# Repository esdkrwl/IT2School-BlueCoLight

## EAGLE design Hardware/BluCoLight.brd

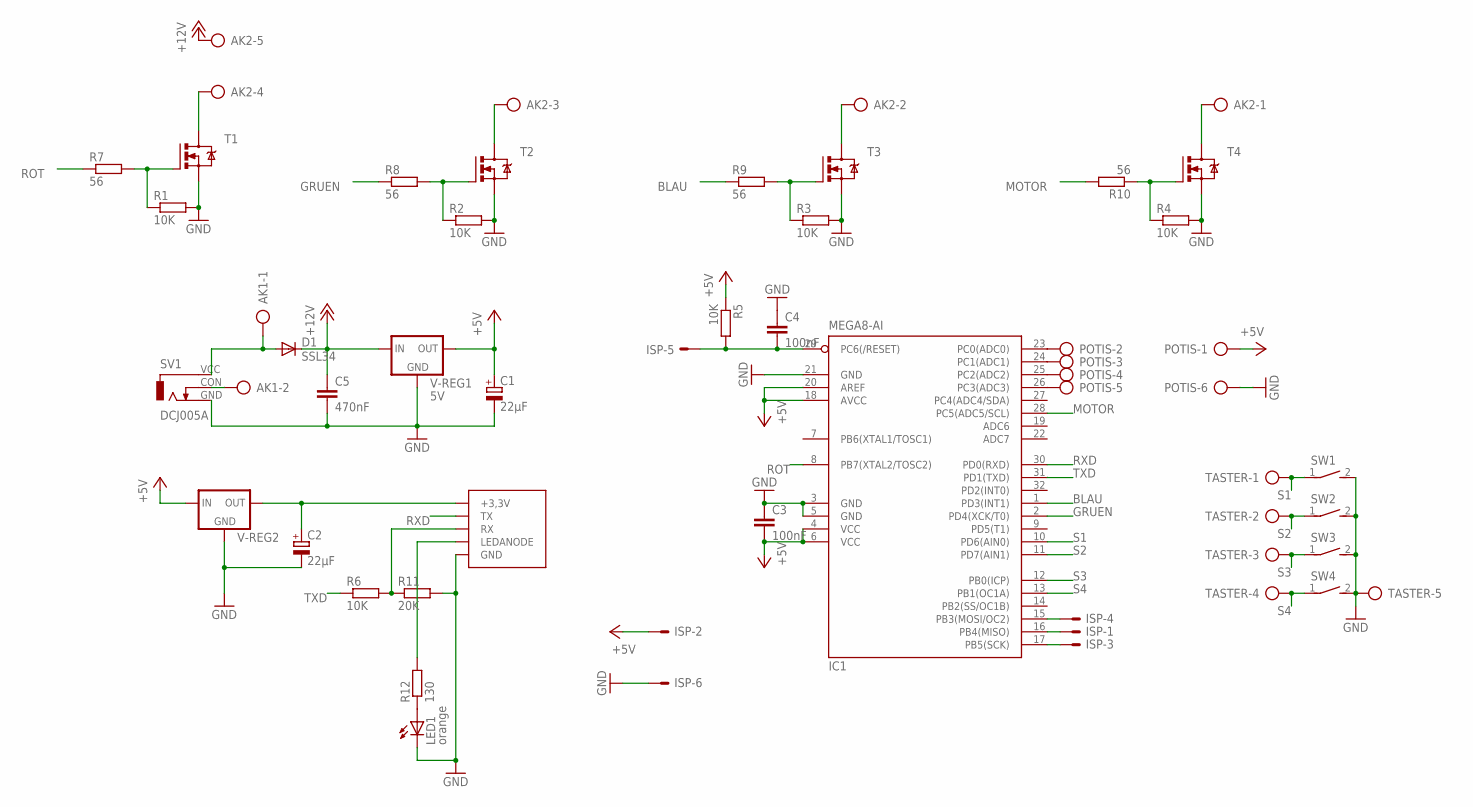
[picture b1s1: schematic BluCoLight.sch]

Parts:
AK1: AK2; AK/2
AK2: AK5AK/5; AK/5
C1, C2: 22µF; 153CLV-0605
C3, C4: 100nF; C0805K
C5: 470nF; C1210K
D1: SSL34; SMC
HC-06: HC-06; HC-06SMD
IC1: MEGA8-AI; TQFP32-08
ISP: ML6E; ML6
LED1: orange; CHIP-LED0603
POTIS: AK6PAD/6; PAD/6
R1, R2, R3, R4, R5, R6: 10K; R0603
R7, R8, R9, R10: 56; R0603
R11: 20K; R0603
R12: 130; R0603
SV1: DCJ005A; DC005A
SW1, SW2, SW3, SW4: TASTER36SMD; 3*6*2.5SMD_TASTER
T1, T2, T3, T4: IRLZ34NSPBFD2PACK; D2PACK
TASTER: AK5PAD/5; PAD/5
V-REG1: 5V; SOT223
V-REG2: AMS1117-3.3SOT223; SOT223

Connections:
+5V: C1.+, C3.2, IC1.4 (VCC), IC1.6 (VCC), IC1.18 (AVCC), IC1.20 (AREF), ISP.2, POTIS.1, R5.1, V-REG1.3 (OUT), V-REG2.3 (IN)
+12V: AK2.5, C5.1, D1.C, V-REG1.1 (IN)
BLAU: IC1.1 (PD3(INT1)), R9.1
GND: C1.-, C2.-, C3.1, C4.1, C5.2, HC-06.P$13 (GND), HC-06.P$21 (GND), HC-06.P$22 (GND), IC1.3 (GND), IC1.5 (GND), IC1.21 (GND), ISP.6, LED1.C, POTIS.6, R1.2, R2.2, R3.2, R4.2, R11.2, SV1.GND (3), SW1.2 (S), SW2.2 (S), SW3.2 (S), SW4.2 (S), T1.3 (S), T2.3 (S), T3.3 (S), T4.3 (S), TASTER.5, V-REG1.2 (GND), V-REG1.4 (GND), V-REG2.1 (GND)
GRUEN: IC1.2 (PD4(XCK/T0)), R8.1
MOTOR: IC1.28 (PC5(ADC5/SCL)), R10.2
unnamed: HC-06.P$24 (LEDANODE), R12.2
unnamed: C4.2, IC1.29 (PC6(/RESET)), ISP.5, R5.2
unnamed: R2.1, R8.2, T2.1 (G)
unnamed: IC1.15 (PB3(MOSI/OC2)), ISP.4
unnamed: R1.1, R7.2, T1.1 (G)
unnamed: AK2.4, T1.2 (D)
unnamed: AK2.3, T2.2 (D)
unnamed: R4.1, R10.1, T4.1 (G)
unnamed: IC1.16 (PB4(MISO)), ISP.1
unnamed: R3.1, R9.2, T3.1 (G)
unnamed: AK2.2, T3.2 (D)
unnamed: IC1.17 (PB5(SCK)), ISP.3
unnamed: AK2.1, T4.2 (D)
unnamed: HC-06.P$2 (RX), R6.2, R11.1
unnamed: LED1.A, R12.1
unnamed: IC1.23 (PC0(ADC0)), POTIS.2
unnamed: IC1.24 (PC1(ADC1)), POTIS.3
unnamed: C2.+, HC-06.P$12 (+3,3V), V-REG2.2 (OUT), V-REG2.4 (OUT)
unnamed: IC1.25 (PC2(ADC2)), POTIS.4
unnamed: IC1.26 (PC3(ADC3)), POTIS.5
unnamed: AK1.2, SV1.CON (2)
unnamed: AK1.1, D1.A, SV1.VCC (1)
ROT: IC1.8 (PB7(XTAL2/TOSC2)), R7.1
RXD: HC-06.P$1 (TX), IC1.30 (PD0(RXD))
S1: IC1.10 (PD6(AIN0)), SW1.1, TASTER.1
S2: IC1.11 (PD7(AIN1)), SW2.1, TASTER.2
S3: IC1.12 (PB0(ICP)), SW3.1, TASTER.3
S4: IC1.13 (PB1(OC1A)), SW4.1, TASTER.4
TXD: IC1.31 (PD1(TXD)), R6.1

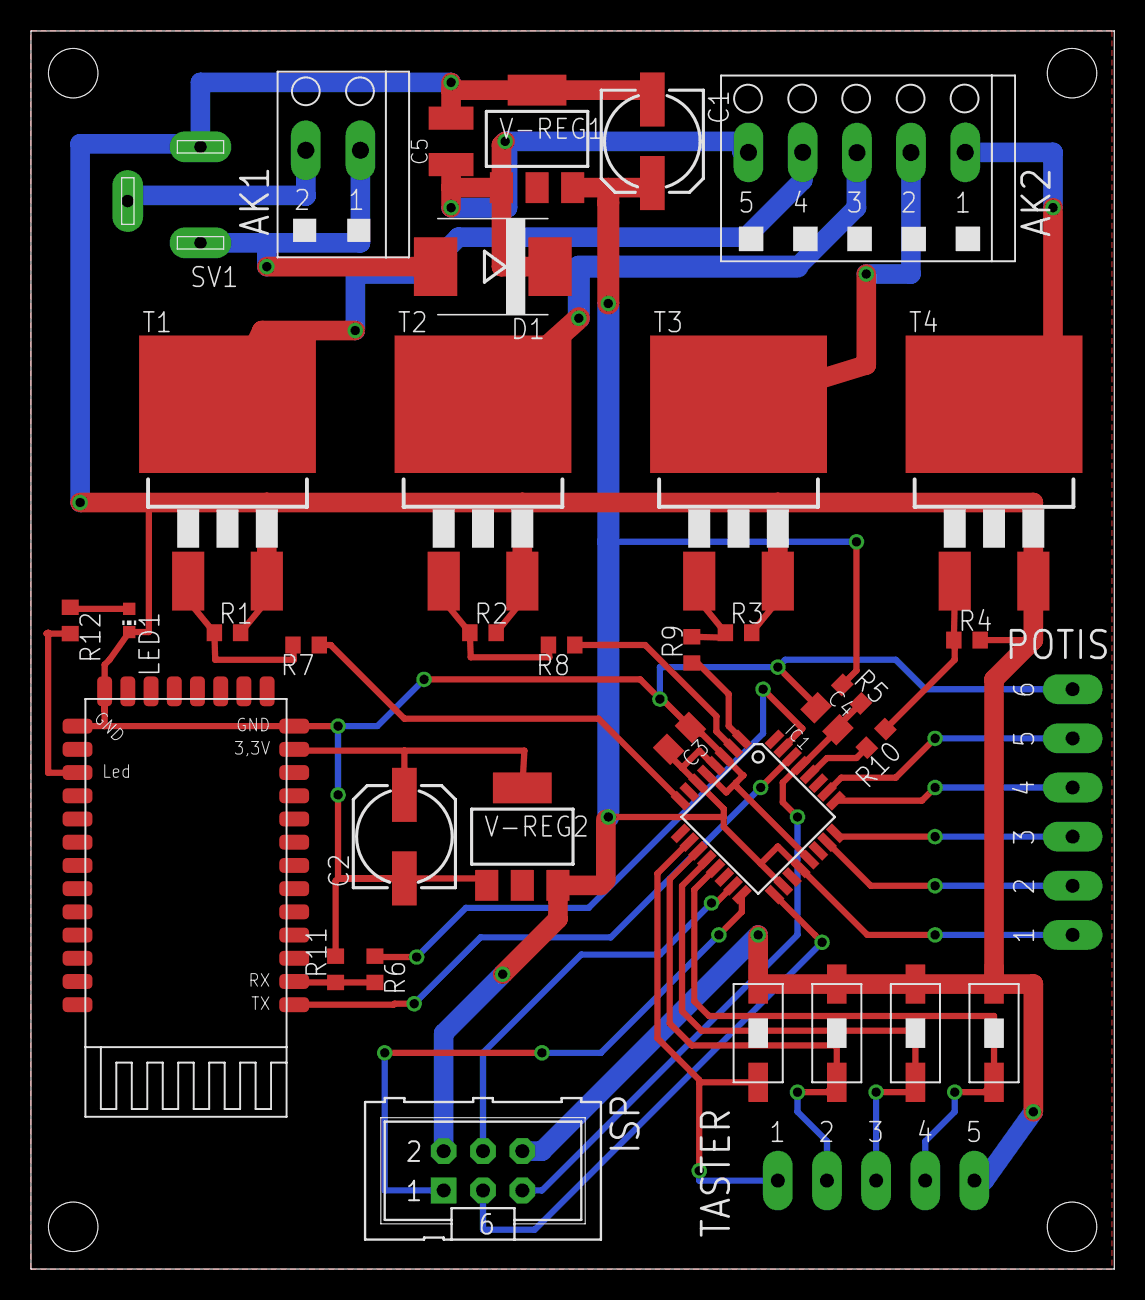
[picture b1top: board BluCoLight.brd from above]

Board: 2 copper layers, 70.0 x 80.0 mm, 37 parts (0 on the bottom side), 35 nets.

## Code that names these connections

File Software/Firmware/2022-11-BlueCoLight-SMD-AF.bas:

$prog &HFF , &HC4 , &HD9 , &HFF                             ' generated. Take care that the chip supports all fuse bytes.
$regfile = "m8adef.dat"
$crystal = 8000000
$baud = 9450
$hwstack = 32
$swstack = 24
$framesize = 24

Gruen Alias Portd.4
Rot Alias Portb.7
Blau Alias Portd.3
Motor Alias Portc.5
Taster1 Alias Pind.6
Taster2 Alias Pind.7
Taster3 Alias Pinb.0
Taster4 Alias Pinb.1

Config Rot = Output
Config Gruen = Output
Config Blau = Output
Config Motor = Output
Config Taster1 = Input
Config Taster2 = Input
Config Taster3 = Input
Config Taster4 = Input

Portd.6 = 1
Portd.7 = 1
Portb.0 = 1
Portb.1 = 1


'wird aufgerufen wenn # empfangen wird
Config Serialin = Buffered , Size = 10 , Bytematch = 35
Config Serialout = Buffered , Size = 100
'Wird von Serialin/out benötigt
Enable Interrupts

'Initialisierung
Dim X As Byte
Dim N As Byte
Dim Error As Bit
Dim Text As String * 22
Dim Zeichenkette As String * 4
Dim A As Byte
Dim Readisprogrammed As Byte
Dim Isprogrammed As Eram Byte
Dim Y As Word
Dim ___rseed As Word

Declare Sub Rename()

Error = 0

Print "Nelli ist mein Fisch";

Rot = 1
Waitms 200
Rot = 0
Gruen = 1
Waitms 200
Gruen = 0
Blau = 1
Waitms 200
Blau = 0
Waitms 200

Do              ''Puffer leeren
Loop Until Ischarwaiting() = 0


Readisprogrammed = Isprogrammed


If Taster1 = 0 AND Taster4 = 0 Then
   Call Rename
End If


If Readisprogrammed = 255 Then
   Call Rename

   If Error = 0 Then
      Readisprogrammed = 1
      Isprogrammed = Readisprogrammed
   End If

End If


'Programmbeginn
Config Timer0 = Timer , Prescale = 1
On Timer0 Regeln
Enable Timer0
Timer0 = 100

Dim Rot_wert As Byte
Dim Gruen_wert As Byte
Dim Blau_wert As Byte
Dim Motor_wert As Byte

Rot_wert = 0
Gruen_wert = 0
Blau_wert = 0
Motor_wert = 0

Do
   If Taster1 = 0 Then
      If Rot_wert < 100 Then Rot_wert = 255 Else Rot_wert = 0
      Waitms 200
   End If
   If Taster2 = 0 Then
      If Gruen_wert < 100 Then Gruen_wert = 255 Else Gruen_wert = 0
      Waitms 200
   End If
   If Taster3 = 0 Then
      If Blau_wert < 100 Then Blau_wert = 255 Else Blau_wert = 0
      Waitms 200
   End If
   If Taster4 = 0 Then
      If Motor_wert < 100 Then Motor_wert = 255 Else Motor_wert = 0
      Waitms 200
   End If
Loop

Regeln:
   If X < 255 Then Incr X Else X = 0
   If X < Rot_wert Then Rot = 1 Else Rot = 0
   If X < Gruen_wert Then Gruen = 1 Else Gruen = 0
   If X < Blau_wert Then Blau = 1 Else Blau = 0
   If X < Motor_wert Then Motor = 1 Else Motor = 0
   Timer0 = 100
Return

Serial0charmatch:
   Stop Timer0
   Text = ""
   While Ischarwaiting() = 1
      A = Inkey()
      If A <> "#" Then Text = Text + Chr(a)
   Wend
   If Left(text , 1) = "R" Then
      Delchars Text , "R"
      Delchars Text , "#"
      Rot_wert = Val(text)
   End If
   If Left(text , 1) = "G" Then
      Delchars Text , "G"
      Delchars Text , "#"
      Gruen_wert = Val(text)
   End If
   If Left(text , 1) = "B" Then
      Delchars Text , "B"
      Delchars Text , "#"
      Blau_wert = Val(text)
   End If
   If Left(text , 1) = "M" Then
      Delchars Text , "M"
      Delchars Text , "#"
      Motor_wert = Val(text)
   End If
   Start Timer0
Return


Sub Rename

   Blau = 1
   Rot = 1
   Gruen = 1
   Motor = 1
   Config Adc = Single , Prescaler = Auto
   Wait 1

   ___rseed = Getadc(0)
   If ___rseed < 20 Then ___rseed = Getadc(1)
   If ___rseed = 0 Then ___rseed = Getadc(2)


   Blau = 0
   Rot = 0
   Gruen = 0
   Motor = 0

   Zeichenkette = ""
   For N = 1 To 3
      X = Rnd(26)
      X = X + 65
      Zeichenkette = Zeichenkette + Chr(x)               '65-90
   Next N

   Print "AT+PIN1234";
   Waitms 250

   Text = ""

   Do
   Loop Until Ischarwaiting() = 1

   Do
      A = Inkey()
      Text = Text + Chr(a)
      Waitms 10
   Loop Until Ischarwaiting() = 0

   If Text <> "OKsetPIN" Then Error = 1

   Print "AT+NAMEBlueCoLight-" ; Zeichenkette;
   Waitms 250


   ''Warte auf neue Daten
   Do
   Loop Until Ischarwaiting() = 1


   Text = ""
   Do
      A = Inkey()
      Text = Text + Chr(a)
      Waitms 10
   Loop Until Ischarwaiting() = 0

   If Text <> "OKsetname" Then Error = 1

   For N = 1 To 5
      If Error = 0 Then
         Toggle Gruen
         Waitms 250
      Else
         Toggle Rot
         Waitms 250
      End If
   Next N

End Sub



End

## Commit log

2022-11-03 Init
2022-11-03 added bascom files
2022-11-03 added eagle libs
2022-11-04 hardware pwm entfernt, da nicht relevant für diesen branch

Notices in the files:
Hardware/BluCoLight.brd:
copyright Tobias Stuckenberg
